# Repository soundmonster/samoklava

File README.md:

# samoklava
## An autogenerated split 36 key keyboard

## Disclaimer

This is an early experimental prototype. Please do not rely on the autogenerated files and double check them manually
before sending them off to a PCB fab. The author and other random strangers on the internet have been able to produce
working keyboard prototypes from this repo; this does not mean that everything will work every time.

The author(s) waive(s) responsibility for any damage or regulatory violations caused by using this software (see
license). Please consult your local regulations around radio frequencies and what's allowed for DIY projects in your
country.

left | right
-|-
 | 

A 5x3 split keyboard with 3 thumb keys. There is nothing unique about the keyboard layout. It's inspired by Corne and
Kyria, and has the exact number of keys needed for the [Miryoku](https://github.com/manna-harbour/miryoku) layout.

The interesting thing about this keyboard is that it's a declarative design:
* Layout is declared using [Ergogen](https://github.com/mrzealot/ergogen/). New: no fork needed!
* The build system uses Ergogen to translate YAML to a KiCad PCB and plate files for FR-4 fab or laser cutting
* uses [kicad-automation-scripts](https://github.com/productize/kicad-automation-scripts) and [FreeRouting](https://github.com/freerouting/freerouting) to **automatically route the traces on the PCB**
* uses [KiKit](https://github.com/yaqwsx/KiKit) to render PCB previews (see top of this file) and production-ready **Gerber files**

## Features

* A slider switch for battery for wireless Promicro clones (tested with nice!nano); the slider can be
  shorted with a jumper if `CONFIG_ZMK_SLEEP` is preferred.
* Wired operation with QMK should be possible but is not tested; TRRS footprints are included and routed. The pinout is
  identical with a five-column Corne sans the RGBLEDs.
* Reset switches are easily accessible. The footprints used are the same as on the Corne.

## How to

If you would like to modify this:
* fork it
* change `config.yaml` to your liking
* push your changes; the `build.yml` GitHub Workflow will pick it up, autoroute and generate Gerbers, all in a zip file.
  See https://github.com/soundmonster/samoklava/actions
* or:
  * make sure to have Docker CLI and NodeJS installed
  * run `make setup clean all`
  * check the `output` folder for KiCad PCBs and Gerbers

See the [workflow](.github/workflows/build.yml) or the [Makefile](Makefile) for more details.
See [my ZMK config](https://github.com/soundmonster/samoklava-zmk-config) for a suggested keymap.

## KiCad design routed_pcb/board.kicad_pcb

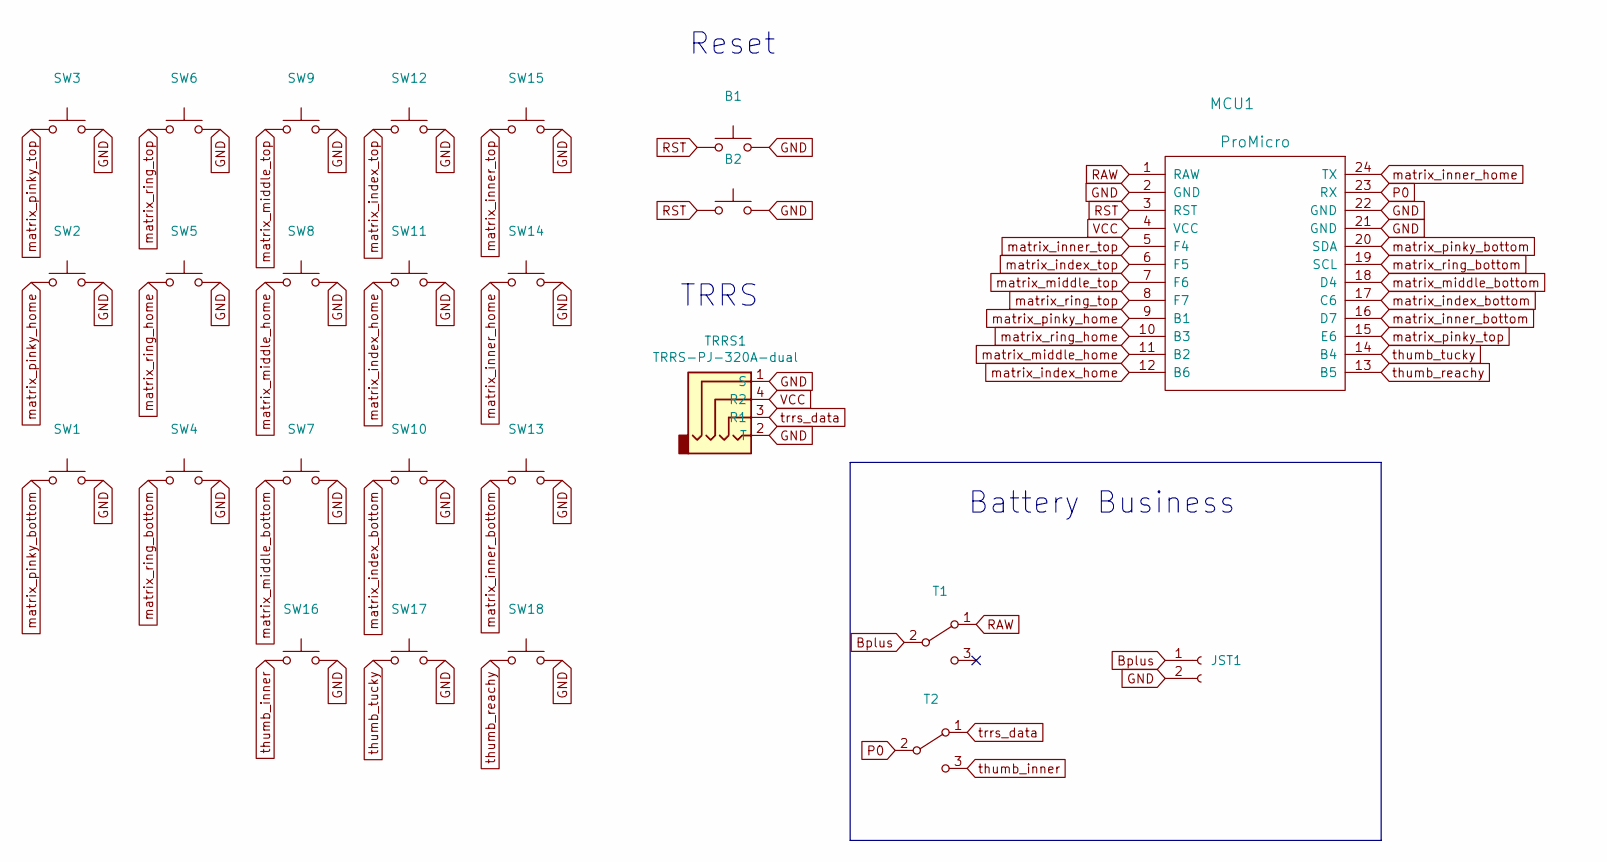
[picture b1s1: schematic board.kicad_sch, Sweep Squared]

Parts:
B1: ResetSW
B2: SW_SPST_B3U-1000P
JST1: JST_PH_S2B-PH-K_02x2.00mm_Angled
MCU1: ProMicro
SW1, SW2, SW3, SW4, SW5, SW6, SW7, SW8, SW9, SW10, SW11, SW12, SW13, SW14, SW15, SW16, SW17, SW18: key-switches
T1, T2: SPDT_C128955
TRRS1: TRRS-PJ-320A-dual

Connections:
/Bplus: JST1.1, T1.2 (B)
/GND: B1.2, B2.2 (1), JST1.2, MCU1.2 (GND), MCU1.21 (GND), MCU1.22 (GND), SW1.2, SW2.2, SW3.2, SW4.2, SW5.2, SW6.2, SW7.2, SW8.2, SW9.2, SW10.2, SW11.2, SW12.2, SW13.2, SW14.2, SW15.2, SW16.2, SW17.2, SW18.2, TRRS1.1 (S), TRRS1.2 (T)
/P0: MCU1.23 (RX), T2.2 (B)
/RAW: MCU1.1 (RAW), T1.1 (A)
/RST: B1.1, B2.1 (2), MCU1.3 (RST)
/VCC: MCU1.4 (VCC), TRRS1.4 (R2)
/matrix_index_bottom: MCU1.17 (C6), SW10.1
/matrix_index_home: MCU1.12 (B6), SW11.1
/matrix_index_top: MCU1.6 (F5), SW12.1
/matrix_inner_bottom: MCU1.16 (D7), SW13.1
/matrix_inner_home: MCU1.24 (TX), SW14.1
/matrix_inner_top: MCU1.5 (F4), SW15.1
/matrix_middle_bottom: MCU1.18 (D4), SW7.1
/matrix_middle_home: MCU1.11 (B2), SW8.1
/matrix_middle_top: MCU1.7 (F6), SW9.1
/matrix_pinky_bottom: MCU1.20 (SDA), SW1.1
/matrix_pinky_home: MCU1.9 (B1), SW2.1
/matrix_pinky_top: MCU1.15 (E6), SW3.1
/matrix_ring_bottom: MCU1.19 (SCL), SW4.1
/matrix_ring_home: MCU1.10 (B3), SW5.1
/matrix_ring_top: MCU1.8 (F7), SW6.1
/thumb_inner: SW16.1, T2.3 (C)
/thumb_reachy: MCU1.13 (B5), SW18.1
/thumb_tucky: MCU1.14 (B4), SW17.1
/trrs_data: T2.1 (A), TRRS1.3 (R1)

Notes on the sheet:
TRRS
Battery Business
Reset

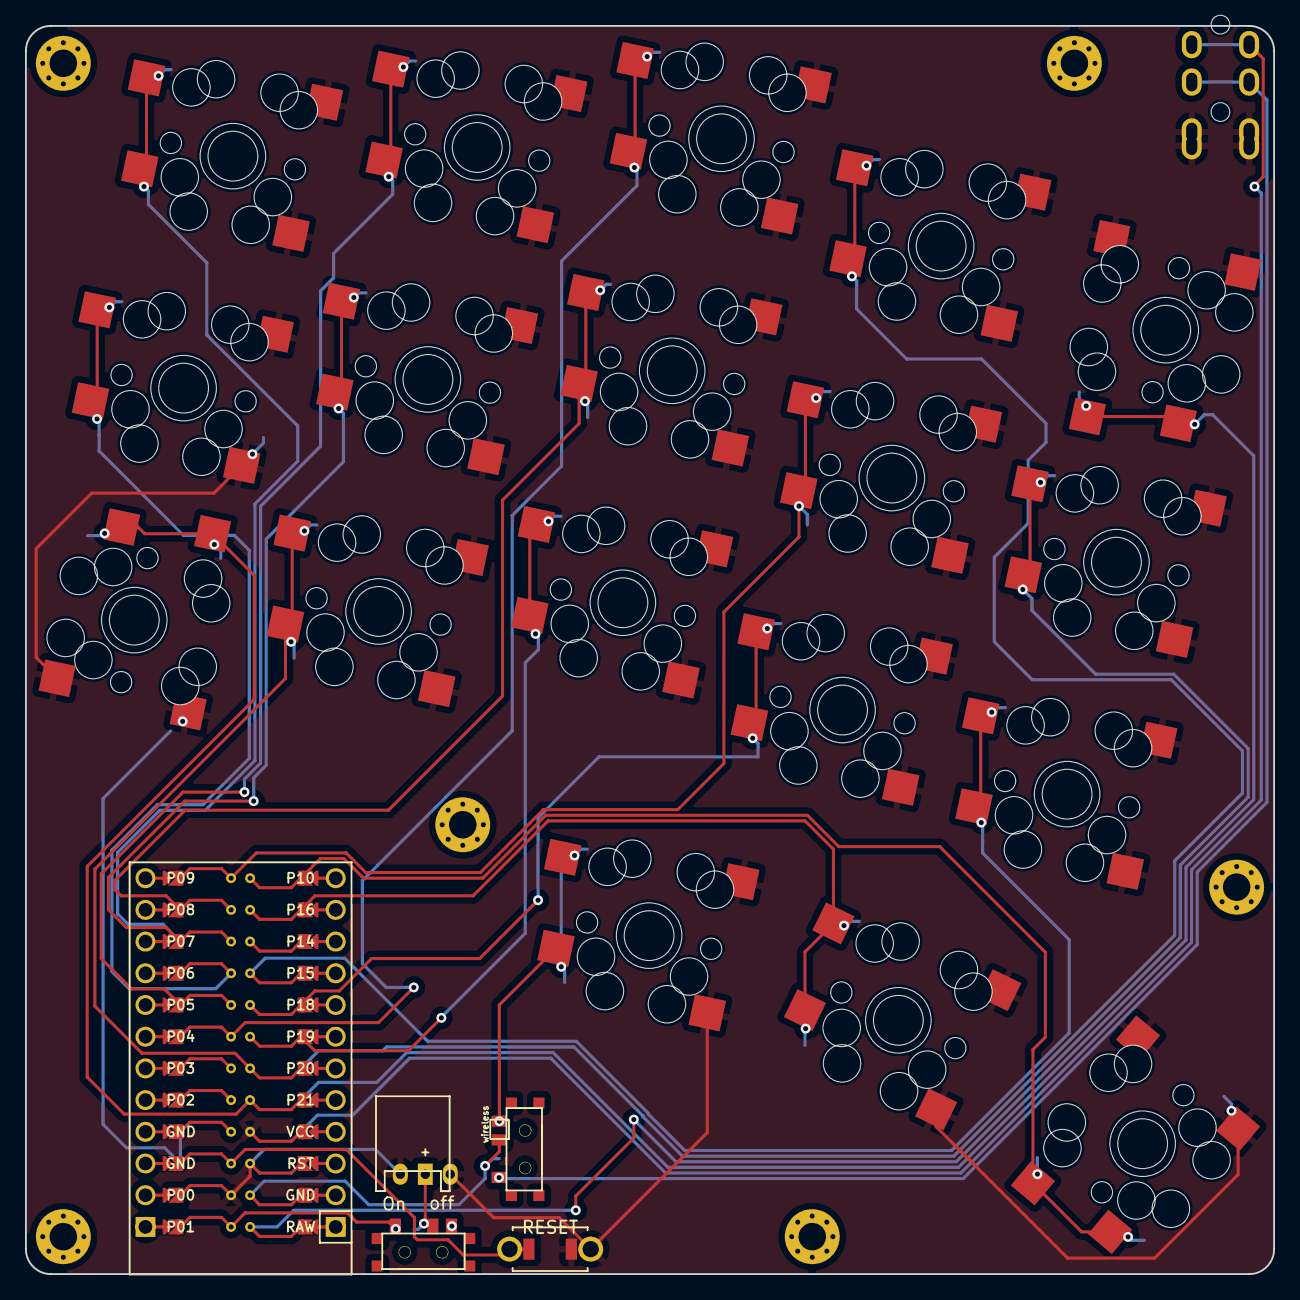
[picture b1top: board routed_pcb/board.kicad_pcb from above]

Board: 2 copper layers, 100.0 x 100.0 mm, 31 parts (0 on the bottom side), 25 nets.

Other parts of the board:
HOLE1, HOLE2, HOLE3, HOLE4, HOLE5, HOLE6: MountingHole_2.2mm_M2_Pad_Via

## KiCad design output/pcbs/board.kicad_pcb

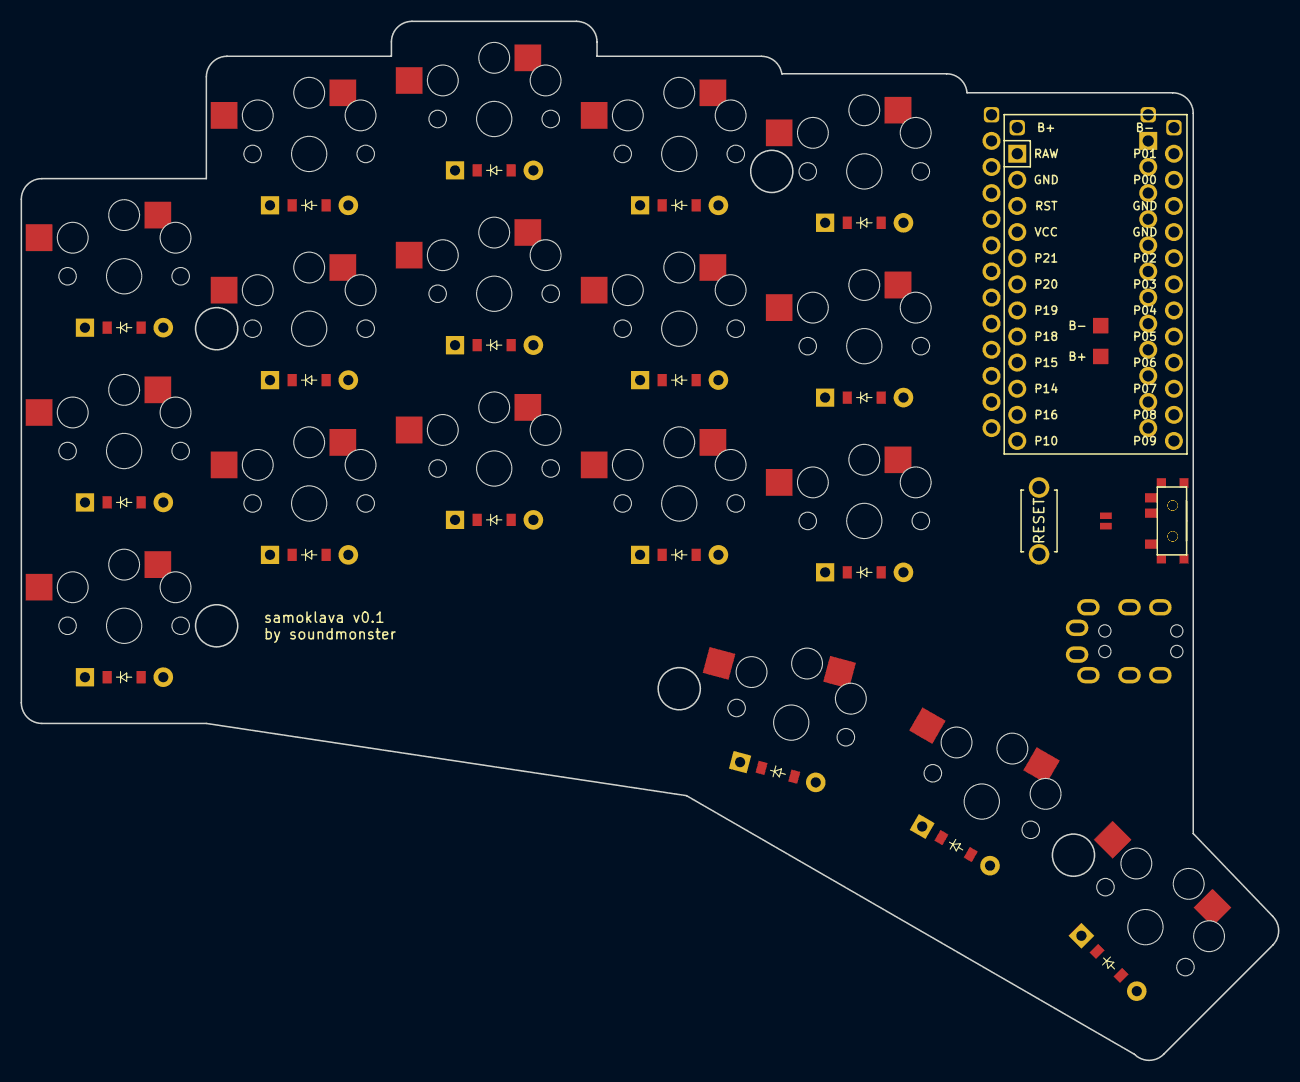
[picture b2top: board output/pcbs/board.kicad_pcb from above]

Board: 2 copper layers, 122.3 x 101.1 mm, 47 parts (0 on the bottom side), 43 nets, no tracks yet.

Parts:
B1: ResetSW
D1, D2, D3, D4, D5, D6, D7, D8, D9, D10, D11, D12, D13, D14, D15, D16, D17, D18: ComboDiode
J1, J2: Jumper
MCU1, MCU2: ProMicro
PAD1, PAD2: SMDPad
S1, S2, S3, S4, S5, S6, S7, S8, S9, S10, S11, S12, S13, S14, S15, S16, S17, S18: PG1350
T1, T2: SPDT_C128955
TRRS1, TRRS2: TRRS-PJ-320A-dual

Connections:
Bminus: MCU1.25, MCU2.25, PAD2.1
Bplus: J1.2, J2.2, MCU1.25, MCU2.25, T1.2, T2.2
Braw: J1.1, J2.1, PAD1.1, T1.1, T2.1
GND: B1.2, MCU1.2, MCU1.15, MCU1.16, MCU2.2, MCU2.15, MCU2.16, TRRS1.3, TRRS2.3
P0: MCU1.14, MCU2.14, TRRS1.4, TRRS2.4
P1: MCU1.13, MCU2.13
P2: MCU1.17, MCU2.17
P3: MCU1.18, MCU2.18
P4: D3.1, D3.2, D6.1, D6.2, D9.1, D9.2, D12.1, D12.2, D15.1, D15.2, MCU1.19, MCU2.19
P5: D2.1, D2.2, D5.1, D5.2, D8.1, D8.2, D11.1, D11.2, D14.1, D14.2, MCU1.20, MCU2.20
P6: D1.1, D1.2, D4.1, D4.2, D7.1, D7.2, D10.1, D10.2, D13.1, D13.2, MCU1.21, MCU2.21
P7: D16.1, D16.2, D17.1, D17.2, D18.1, D18.2, MCU1.22, MCU2.22
P8: MCU1.23, MCU2.23
P9: MCU1.24, MCU2.24
P10: MCU1.12, MCU2.12
P14: MCU1.10, MCU2.10, S13.2, S14.2, S15.2, S18.2
P15: MCU1.9, MCU2.9, S10.2, S11.2, S12.2, S17.2
P16: MCU1.11, MCU2.11
P18: MCU1.8, MCU2.8, S7.2, S8.2, S9.2, S16.2
P19: MCU1.7, MCU2.7, S4.2, S5.2, S6.2
P20: MCU1.6, MCU2.6, S1.2, S2.2, S3.2
P21: MCU1.5, MCU2.5
RAW: MCU1.1, MCU2.1
RST: B1.1, MCU1.3, MCU2.3
VCC: MCU1.4, MCU2.4, TRRS1.2, TRRS2.2
far_thumb: D18.1, D18.2, S18.1
home_thumb: D17.1, D17.2, S17.1
index_bottom: D10.1, D10.2, S10.1
index_home: D11.1, D11.2, S11.1
index_top: D12.1, D12.2, S12.1
inner_bottom: D13.1, D13.2, S13.1
inner_home: D14.1, D14.2, S14.1
inner_top: D15.1, D15.2, S15.1
middle_bottom: D7.1, D7.2, S7.1
middle_home: D8.1, D8.2, S8.1
middle_top: D9.1, D9.2, S9.1
near_thumb: D16.1, D16.2, S16.1
pinky_bottom: D1.1, D1.2, S1.1
pinky_home: D2.1, D2.2, S2.1
pinky_top: D3.1, D3.2, S3.1
ring_bottom: D4.1, D4.2, S4.1
ring_home: D5.1, D5.2, S5.1
ring_top: D6.1, D6.2, S6.1

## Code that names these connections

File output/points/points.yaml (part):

matrix_pinky_bottom:
    x: 18
    'y': 0
    r: 0
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                        - -5
        column_net: P21
        row_net: P7
        name: matrix_pinky_bottom
        colrow: pinky_bottom
        col: &ref_0
            stagger: 0
            spread: 18
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            rows: {}
            name: pinky
        row: bottom
matrix_pinky_home:
    x: 18
    'y': 17
    r: 0
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                        - -5
        column_net: P21
        row_net: P6
        name: matrix_pinky_home
        colrow: pinky_home
        col: *ref_0
        row: home
matrix_pinky_top:
    x: 18
    'y': 34
    r: 0
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                        - -5
        column_net: P21
        row_net: P5
        name: matrix_pinky_top
        colrow: pinky_top
        col: *ref_0
        row: top
matrix_ring_bottom:
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
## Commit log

2021-09-03 Add Makefile
2021-09-03 Add output
2021-09-03 rofl > lol
2021-09-10 First working version
2021-09-10 Some updates, not ready for publishing yet
2021-09-10 Images side by side
2021-09-10 Some marketing :rofl:
2021-09-11 Better wording
2021-09-16 Rename main keyboard file
2021-09-16 Wip Makefile
2021-09-18 First working version of Makefile
2021-09-29 rename
2021-09-29 Remove images/
2021-09-29 Explain the name
2021-10-13 A probably working version
2021-10-14 Fix nested gerber dirs
2021-10-14 Make mounting holes a bit larger
2021-10-14 Add output files
2021-11-08 Fix pins for the matrix
2021-11-08 Add board dims
2021-11-08 Upgrade ergogen fork version
2021-11-08 Wip: yaml works, routing is broken
2021-11-08 Still wip
2021-11-09 Minor progress
2021-11-10 Use latest node
2021-11-11 Post rebase cleanup
2021-11-11 Readd output folder
2021-11-11 finish up
2021-11-11 Fix pinout (#3)
    * Fix pin compatibility with Corne
    * Add battery pins for nice!nano
    * Add reset microswitch
    * Fix TRRS reversibility
    * Add a slider to shut off battery
2021-11-13 Use a better reset button footprint
2021-11-13 Use a better reset button footprint (#6)
2021-11-13 Use dark PCB style; remove custom style file
2021-11-29 Add first workflow draft
2021-11-29 debug
2021-11-29 Add checkout
2021-11-29 Clear output folder
2021-11-29 Use another node container
2021-11-29 Force npm install
2021-11-29 Try yet another node container
2021-11-29 try pure nodejs action
2021-11-30 Store output
2021-11-30 Add action for DSN export
2021-11-30 Wip action
2021-12-01 Specify paths
2021-12-01 Debug action
2021-12-01 Moar debug
2021-12-01 Use thet python script for real
2021-12-01 Try to capture xvfb
2021-12-01 wip capture
2021-12-01 debug kicad config folder
2021-12-01 strace
2021-12-01 Strace forks too
2021-12-01 Try injecting strace into the scipt that calls pcbnew
2021-12-01 fix broken package file
2021-12-01 Move Kicad config to new $HOME
2021-12-01 First try at full autorouting circle
2021-12-01 Add missing actions
2021-12-01 Add Gerbers export
2021-12-01 Try to fix the SES import
2021-12-01 Make paths for kikit absolute
2021-12-10 try recording
2021-12-10 wip record
2021-12-10 Overwrite the routed PCB
2021-12-10 Turn on gerber export again
2021-12-10 Fix plate file names
2021-12-10 Rename output file
2021-12-10 Update instructions
2021-12-10 Add autorouting via GitHub Workflow (#8)
2021-12-10 Add an order number placeholder on the top plate
2021-12-10 Add an order number placeholder on the top plate (#9)
2021-12-10 Upload board images separately
2021-12-10 Remove unclear TODO
2021-12-10 Fix typo
2021-12-10 Improve README
2021-12-10 Fix gibberish in README
2021-12-12 Test a more dramatic pinky stagger
2022-01-06 Update to ergogen 3.1.0 (#13)
2022-01-06 Add MIT license
2022-01-06 Add MIT license (#14)
2022-01-06 Update board renders
2022-01-06 Add warning
2022-01-06 Revert "Add warning"
    This reverts commit 66e57baf39782c002756d8bd98580254902e9feb.
2022-01-19 main- | Adds text
2022-01-20 choc_mini- | Adds choc minis
2022-01-20 choc_mini- | Corrects outline
2022-01-21 choc_mini- | Moves back to soundastem fork
2022-01-21 choc_mini- | Updates package lock
2022-01-21 choc_mini- | Updates outline
2022-02-21 choc_mini- | Changes rotation
2022-02-21 choc_mini- | Patches hole
2022-02-21 choc_mini- | Removes pin names and reset text from keyboard
2022-02-21 choc_mini- | Changes rotation of the text
2022-02-21 choc_mini- | Generates images
2022-02-21 choc_mini- | Replaces images
2022-03-07 choc_mini- | Some more improvements
2022-05-01 choc_mini- | WIP sweep
2022-05-01 choc_mini- | Version without logo
2022-05-01 choc_mini- | Sweep test
2022-05-01 choc_mini- | Changed far thumb forautorotue
2022-05-01 choc_mini- | Puts image on both sides
2022-05-01 choc_mini- | Updatesbroom
2022-05-01 choc_mini- | Fixes autoroute
2022-05-01 choc_mini- | Adds images
2022-05-02 choc_mini- | Some minor changes
2022-05-02 choc_mini- | Updates images
2022-08-28 Use 24-pin promicro footprint; uniformly align sliders; move battery pads
2022-08-28 Update renders
2022-08-28 Use 24-pin promicro footprint; unifomly align sliders (#23)
2023-05-29 initial fork. Added number and function rows
2023-08-05 Upgrade to latest Ergogen
2023-08-05 Migrate basic key layout and all outlines
2023-08-06 Make it a 'bundle'
2023-08-06 Fix text footprint
2023-08-07 Wip wrt nets
2023-08-11 This might actually work
2023-08-21 Upgrade to Ergogen v4 (#25)
    * Upgrade to Ergogen v4 and its new positioning / offset rules
    * Make Samoklava a "bundle" that includes all of its custom footprints
2023-08-21 Remove duplicate build script and clean up Readme
2023-10-28 made ergogen config for sweep squared
2023-10-28 removed top and bottom plate actions, renamed pcb
2023-10-28 routing bugs
2023-10-28 added mounting, case
2023-10-28 added routed pcb
2023-10-28 board cleanup
2023-10-28 added plate
2023-11-08 Remove reference about the extra pins from the readme
2023-11-10 Update README.md (#26)
2023-11-10 removed helpers, added outlines
2023-11-11 updated config file
2023-11-11 added gateron switches
2023-11-11 updated control area and outlines
2023-11-11 wireless slider bug
2023-11-11 routed new pcb
2023-11-11 added in schematic
2023-11-11 updated designator in footprints
2023-11-11 update routed pcb to same as updated config
2024-01-19 Fix pcbdraw commands
2024-01-24 Fix name
2024-01-24 Fix Gerber generation
2024-02-10 Fix pcbdraw/kikit calls (#29)
2024-02-14 Put Promicro silk prints on the right sides
2024-07-07 Change to corne 3x6 layout
2024-10-23 Upgrade actions and Node to 21.x
